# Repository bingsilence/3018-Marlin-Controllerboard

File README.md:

# 3018 STM32 Marlin Controllerboard
A controllerboard for the 3018 CNC, utilize an STM32 and TMC drivers. 

## Specification
* 24 V
* 6 end stops, 2 for each axis
* Fan controller
* LED controller
* Display from Delta printer
* Tool probing

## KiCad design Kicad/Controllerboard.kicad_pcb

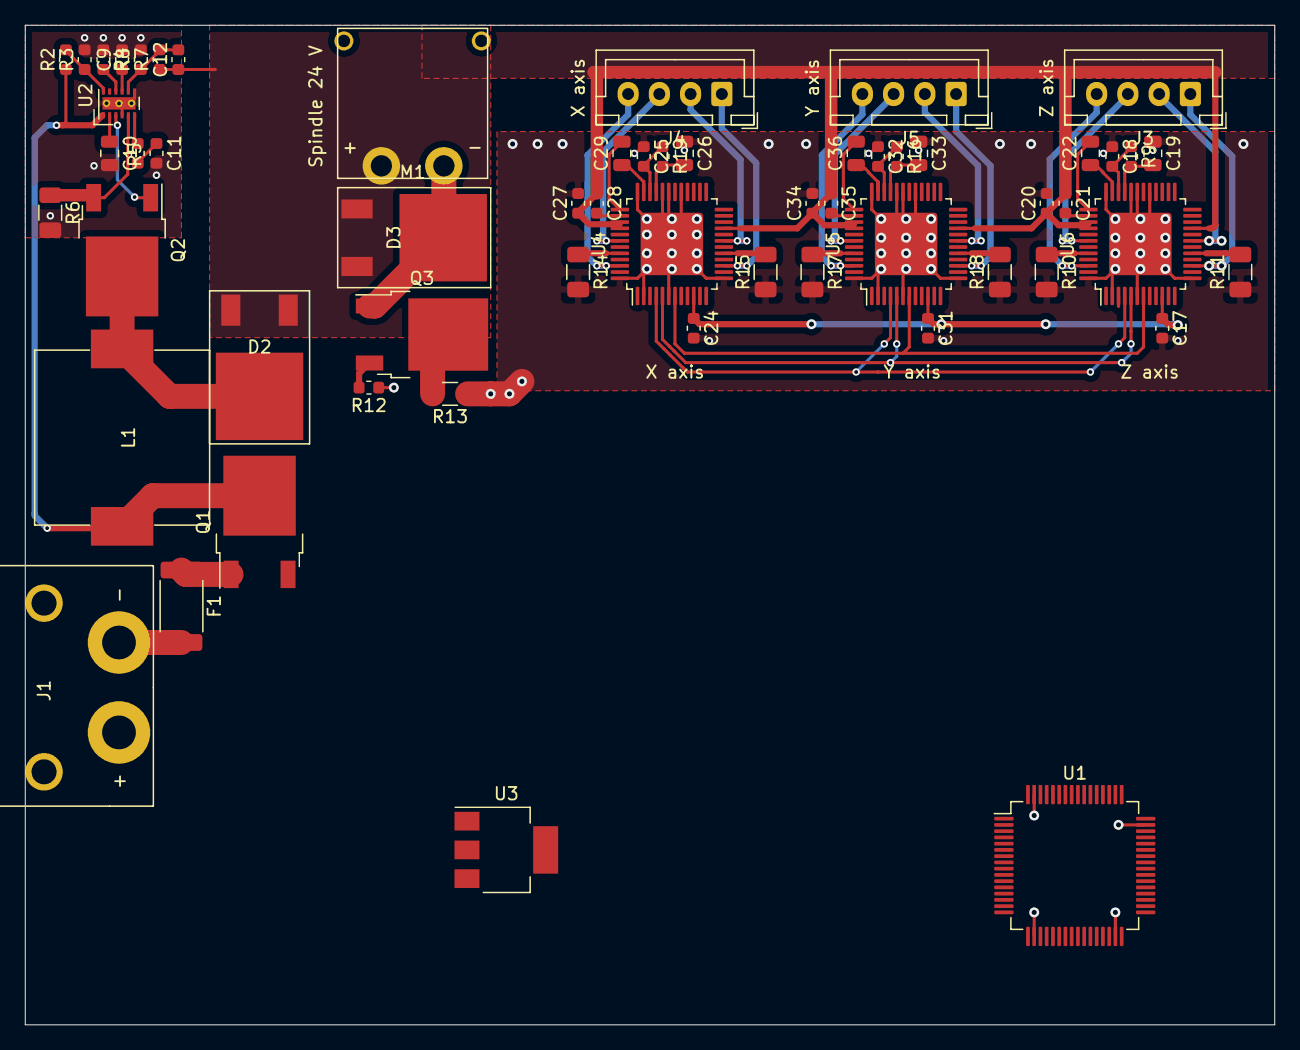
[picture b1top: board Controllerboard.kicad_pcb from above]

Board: 2 copper layers, 100.0 x 80.0 mm, 58 parts (0 on the bottom side), 55 nets.

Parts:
C9, C11, C12: F; C_0603_1608Metric
C10, C19, C26, C33: 4.7µF; C_0805_2012Metric
C17, C20, C21, C24, C27, C28, C31, C34, C35: 100nF; C_0603_1608Metric
C18, C25, C32: 470nF; C_0603_1608Metric
C22, C29, C36: 22nF63V; C_0805_2012Metric
D2: D_Schottky; DPAK
D3: D; DPAK
F1: 15A; Fuse_2512_6332Metric
J1: Conn_01x02_Male; XT60PW-F
J3: ZAXIS; JST_XH_B4B-XH-A_1x04_P2.50mm_Vertical
J4: XAXIS; JST_XH_B4B-XH-A_1x04_P2.50mm_Vertical
J5: YAXIS; JST_XH_B4B-XH-A_1x04_P2.50mm_Vertical
L1: 2.2µF; SRP1265A
M1: Motor_DC; XT30PW-M
Q1: Q_PMOS_DSG; TO-252-2
Q2: Q_NMOS_GDS; TO-252-2
Q3: Q_NMOS_DSG; TO-252-2
R2, R3, R5, R7, R8: R; R_0603_1608Metric
R4, R12: 10k; R_0603_1608Metric
R6, R13: 0.01R; R_1206_3216Metric
R9, R16, R19: 2R2; R_0603_1608Metric
R10, R11, R14, R15, R17, R18: 0.5W1206; R_1206_3216Metric
U1: STM32F103RCTx; LQFP-64_10x10mm_P0.5mm
U2: LM5155; WSON-12-1EP_3x2mm_P0.5mm_EP1x2.65_ThermalVias
U3: AMS1117-3.3; SOT-223-3_TabPin2
U4, U5, U6: TMC2130-TA; TQFP-48-1EP_7x7mm_P0.5mm_EP5x5mm

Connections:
+3V3: C17.1, C24.1, C31.1, U1.1, U1.19, U1.32, U1.48, U1.64, U3.2, U4.10, U5.10, U6.10
+24V: C12.1, C20.1, C21.1, C27.1, C28.1, C34.1, C35.1, D2.1, D3.1, M1.1, R7.1, U4.21, U4.39, U4.40, U5.21, U5.39, U5.40, U6.21, U6.39, U6.40
+VDC: L1.1, Q1.2, R2.1, U2.1
GND: C9.2, C10.2, C11.2, C17.2, C18.1, C19.1, C20.2, C24.2, C25.1, C26.1, C27.2, C31.2, C32.1, C33.1, C34.2, J1.1, R3.2, R4.1, R6.2, R8.2, R10.2, R11.1, R12.1, R13.1, R14.2, R15.1, R17.2, R18.1, U1.18, U1.31, U1.47, U1.63, U2.4, U2.7, U2.13, U3.1, U4.2, U4.6, U4.13, U4.29, U4.31, U4.32, U4.36, U4.48, U4.49, U5.2, U5.6, U5.13, U5.29, U5.31, U5.32, U5.36, U5.48, U5.49, U6.2, U6.6, U6.13, U6.29, U6.31, U6.32, U6.36, U6.48, U6.49
unnamed: C9.1, U2.9
unnamed: C10.1, U2.2
unnamed: C11.1, R5.2
unnamed: C12.2, R7.2, R8.1, U2.8
unnamed: C18.2, R9.1, U6.34
unnamed: C19.2, R9.2, U6.33
unnamed: C21.2, U6.38
unnamed: C22.1, U6.35
unnamed: C22.2, U6.37
unnamed: C25.2, R19.1, U4.34
unnamed: C26.2, R19.2, U4.33
unnamed: C28.2, U4.38
unnamed: C29.1, U4.35
unnamed: C29.2, U4.37
unnamed: C32.2, R16.1, U5.34
unnamed: C33.2, R16.2, U5.33
unnamed: C35.2, U5.38
unnamed: C36.1, U5.35
unnamed: C36.2, U5.37
unnamed: D2.2, L1.2, Q2.2
unnamed: D3.2, M1.2, Q3.1
unnamed: F1.1, Q1.1
unnamed: F1.2, J1.2
unnamed: J3.1, U6.15
unnamed: J3.2, U6.19
unnamed: J3.3, U6.42
unnamed: J3.4, U6.46
unnamed: J4.1, U4.15
unnamed: J4.2, U4.19
unnamed: J4.3, U4.42
unnamed: J4.4, U4.46
unnamed: J5.1, U5.15
unnamed: J5.2, U5.19
unnamed: J5.3, U5.42
unnamed: J5.4, U5.46
unnamed: Q2.1, U2.3
unnamed: Q2.3, R6.1, U2.5
unnamed: Q3.2, R13.2
unnamed: R2.2, R3.1, U2.12
unnamed: R4.2, U2.10
unnamed: R5.1, U2.6
unnamed: R10.1, U6.44
unnamed: R11.2, U6.17
unnamed: R14.1, U4.44
unnamed: R15.2, U4.17
unnamed: R17.1, U5.44
unnamed: R18.2, U5.17
SCK: U4.4, U5.4, U6.4
SDI: U4.5, U5.5, U6.5
SDO: U4.7, U5.7, U6.7
SPINDLE_PWM: Q3.3, R12.2

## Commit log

2020-01-13 Create Kicad project
2020-01-13 Created schematics for parts of system
2020-01-13 Added stepper driver and componets and power management
2020-01-13 Added spindle sheet
2020-01-14 Added TMC2130 to board and routed
2020-01-14 Completed the TMC2130 layout and Boost converter layout
2020-01-14 End of day commit
2020-01-28 Added step files and Marlin 2.0
2020-01-28 Changed firmware to GRBL v1.1 for Mega
2020-01-28 Changed to RAMPS 1.4 and 2 homing cycle
2020-01-28 Use NC endstops
    It is safer to use NC endstops, since if one cable broke, the machine will stop and think it hit an endstop.
2020-01-28 Disable internal pullup for limit switch and decreased feed override to 120%
2020-01-31 Added dimensions as max travel and doublechecked spindle pin
    spindle pin D8 is correct as heatbed pin in Ramps 1.3
2020-02-02 Disable internal pull-up and add gitignore
2020-02-02 Added ugsplatform software
